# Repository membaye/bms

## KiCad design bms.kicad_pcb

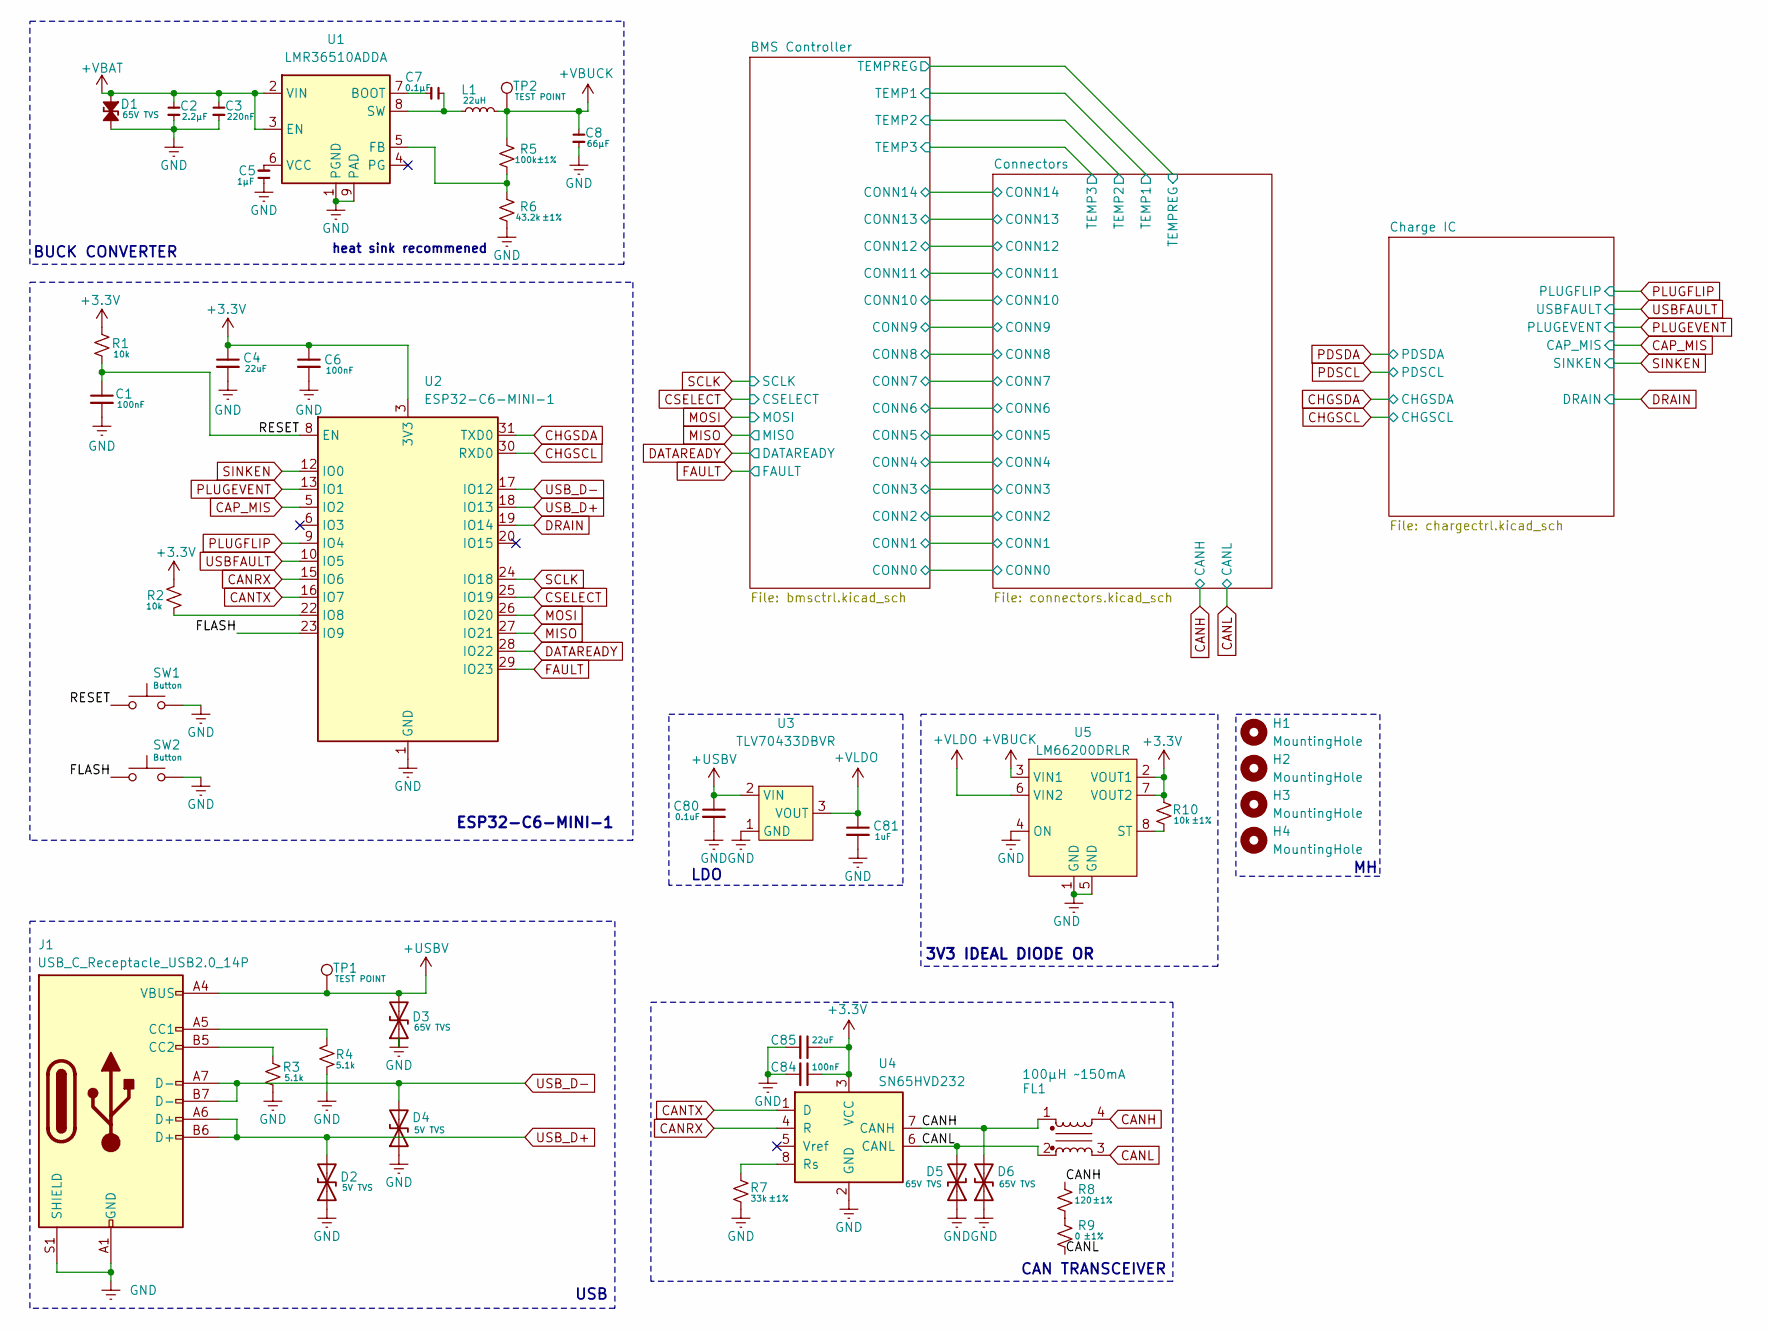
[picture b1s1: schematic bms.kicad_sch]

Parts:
C1, C6: 100nF; C_0402_1005Metric_Pad0.74x0.62mm_HandSolder; LCSC# C1525
C2: 2.2µF; C_0402_1005Metric_Pad0.74x0.62mm_HandSolder
C3: 220nF; C_0402_1005Metric_Pad0.74x0.62mm_HandSolder
C4, C85: 22uF; C_0402_1005Metric_Pad0.74x0.62mm_HandSolder; LCSC# C87997
C5: 1µF; C_0402_1005Metric_Pad0.74x0.62mm_HandSolder
C7: 0.1µF; C_0402_1005Metric_Pad0.74x0.62mm_HandSolder
C8: 66µF; C_0402_1005Metric_Pad0.74x0.62mm_HandSolder
C80: 0.1uF; C_0402_1005Metric_Pad0.74x0.62mm_HandSolder; LCSC# C87997
C81: 1uF; C_0402_1005Metric_Pad0.74x0.62mm_HandSolder; LCSC# C87997
C84: 100nF; C_0402_1005Metric_Pad0.74x0.62mm_HandSolder; LCSC# C87997
D1: 65V TVS; D_0402_1005Metric_Pad0.77x0.64mm_HandSolder
D2, D4: 5V TVS; D_0402_1005Metric_Pad0.77x0.64mm_HandSolder; LCSC# C316043
D3, D5, D6: 65V TVS; D_0402_1005Metric_Pad0.77x0.64mm_HandSolder; LCSC# C316043
FL1: 100µH ~150mA; Crystal_SMD_TXC_7M-4Pin_3.2x2.5mm; MPN C42394181
H1, H2, H3, H4: MountingHole; MountingHole_3.2mm_M3
J1: USB_C_Receptacle_USB2.0_14P; USB_C_Receptacle_GCT_USB4105-xx-A_16P_TopMnt_Horizontal; MPN C165948; LCSC# C165948
L1: 22uH; L_Ferrocore_DLG-0403; MPN C2929420
R1, R2: 10k; R_0402_1005Metric_Pad0.72x0.64mm_HandSolder; LCSC# C190095
R3, R4: 5.1k; R_0402_1005Metric_Pad0.72x0.64mm_HandSolder; LCSC# C490833
R5: 100k; R_0402_1005Metric_Pad0.72x0.64mm_HandSolder; Tolerance ±1%
R6: 43.2k; R_0402_1005Metric_Pad0.72x0.64mm_HandSolder; Tolerance ±1%
R7: 33k; R_0402_1005Metric_Pad0.72x0.64mm_HandSolder; Tolerance ±1%
R8: 120; R_0402_1005Metric_Pad0.72x0.64mm_HandSolder; Tolerance ±1%
R9: 0; R_0402_1005Metric_Pad0.72x0.64mm_HandSolder; Tolerance ±1%
R10: 10k; R_0402_1005Metric_Pad0.72x0.64mm_HandSolder; Tolerance ±1%
SW1, SW2: Button; SW-SMD_L3.9-W3.0-P4.45; LCSC# C720477
TP1, TP2: TEST POINT; TestPoint_Pad_1.0x1.0mm
U1: LMR36510ADDA; Texas_HTSOP-8-1EP_3.9x4.9mm_P1.27mm_EP2.95x4.9mm_Mask2.4x3.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
U2: ESP32-C6-MINI-1; LCSC# C5736265
U3: TLV70433DBVR; SOT-23-5_HandSoldering
U4: SN65HVD232; SOIC-8_3.9x4.9mm_P1.27mm
U5: LM66200DRLR; SOT-23-8

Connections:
+3.3V: C4.1, C6.1, C84.1, C85.1, R1.1, R2.1, R10.2, U2.3 (3V3), U4.3 (VCC), U5.2 (VOUT1), U5.7 (VOUT2); also elsewhere on the board
+USBV: C80.1, D3.2 (A2), J1.A4 (VBUS), J1.A9 (VBUS), J1.B4 (VBUS), J1.B9 (VBUS), TP1.1, U3.2 (VIN); also elsewhere on the board
+VBAT: C2.1, C3.1, D1.1 (A1), U1.2 (VIN), U1.3 (EN); also elsewhere on the board
+VBUCK: C8.1, L1.2, R5.1, TP2.1, U5.3 (VIN1)
+VLDO: C81.1, U3.3 (VOUT), U5.6 (VIN2)
/FLASH: SW2.1, U2.23 (IO9)
/RESET: C1.1, R1.2, SW1.1, U2.8 (EN)
CANH: D6.2 (A2), FL1.1, FL1.4, R8.2, U4.7 (CANH); also elsewhere on the board
CANL: D5.2 (A2), FL1.2, FL1.3, R9.1, U4.6 (CANL); also elsewhere on the board
CANRX: U2.15 (IO6), U4.4 (R)
CANTX: U2.16 (IO7), U4.1 (D)
CAP_MIS: U2.5 (IO2); also elsewhere on the board
CHGSCL: U2.30 (RXD0); also elsewhere on the board
CHGSDA: U2.31 (TXD0); also elsewhere on the board
CSELECT: U2.25 (IO19); also elsewhere on the board
DATAREADY: U2.28 (IO22); also elsewhere on the board
DRAIN: U2.19 (IO14); also elsewhere on the board
FAULT: U2.29 (IO23); also elsewhere on the board
GND: C1.2, C2.2, C3.2, C4.2, C5.1, C6.2, C8.2, C80.2, C81.2, C84.2, C85.2, D1.2 (A2), D2.1 (A1), D3.1 (A1), D4.1 (A1), D5.1 (A1), D6.1 (A1), J1.A1 (GND), J1.A12 (GND), J1.B1 (GND), J1.B12 (GND), J1.S1 (SHIELD), R3.2, R4.2, R6.2, R7.1, SW1.2, SW2.2, U1.1 (PGND), U1.9 (PAD), U2.1 (GND), U2.2 (GND), U2.11 (GND), U2.14 (GND), U2.36 (GND), U2.37 (GND), U2.38 (GND), U2.39 (GND), U2.40 (GND), U2.41 (GND), U2.42 (GND), U2.43 (GND), U2.44 (GND), U2.45 (GND), U2.46 (GND), U2.47 (GND), U2.48 (GND), U2.49 (GND), U2.50 (GND), U2.51 (GND), U2.52 (GND), U2.53 (GND), U3.1 (GND), U4.2 (GND), U5.1 (GND), U5.4 (ON), U5.5 (GND); also elsewhere on the board
MISO: U2.27 (IO21); also elsewhere on the board
MOSI: U2.26 (IO20); also elsewhere on the board
unnamed: J1.A5 (CC1), R4.1
unnamed: J1.B5 (CC2), R3.1
unnamed: R8.1, R9.2
unnamed: C7.2, U1.7 (BOOT)
unnamed: R5.2, R6.1, U1.5 (FB)
unnamed: C7.1, L1.1, U1.8 (SW)
unnamed: C5.2, U1.6 (VCC)
unnamed: R2.2, U2.22 (IO8)
unnamed: R7.2, U4.8 (Rs)
unnamed: R10.1, U5.8 (ST)
PLUGEVENT: U2.13 (IO1); also elsewhere on the board
PLUGFLIP: U2.9 (IO4); also elsewhere on the board
SCLK: U2.24 (IO18); also elsewhere on the board
SINKEN: U2.12 (IO0); also elsewhere on the board
USBFAULT: U2.10 (IO5); also elsewhere on the board
USB_D+: D2.2 (A2), J1.A6 (D+), J1.B6 (D+), U2.18 (IO13)
USB_D-: D4.2 (A2), J1.A7 (D-), J1.B7 (D-), U2.17 (IO12)

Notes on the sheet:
ESP32-C6-MINI-1
heat sink recommened
BUCK CONVERTER
USB
LDO
CAN TRANSCEIVER
3V3 IDEAL DIODE OR

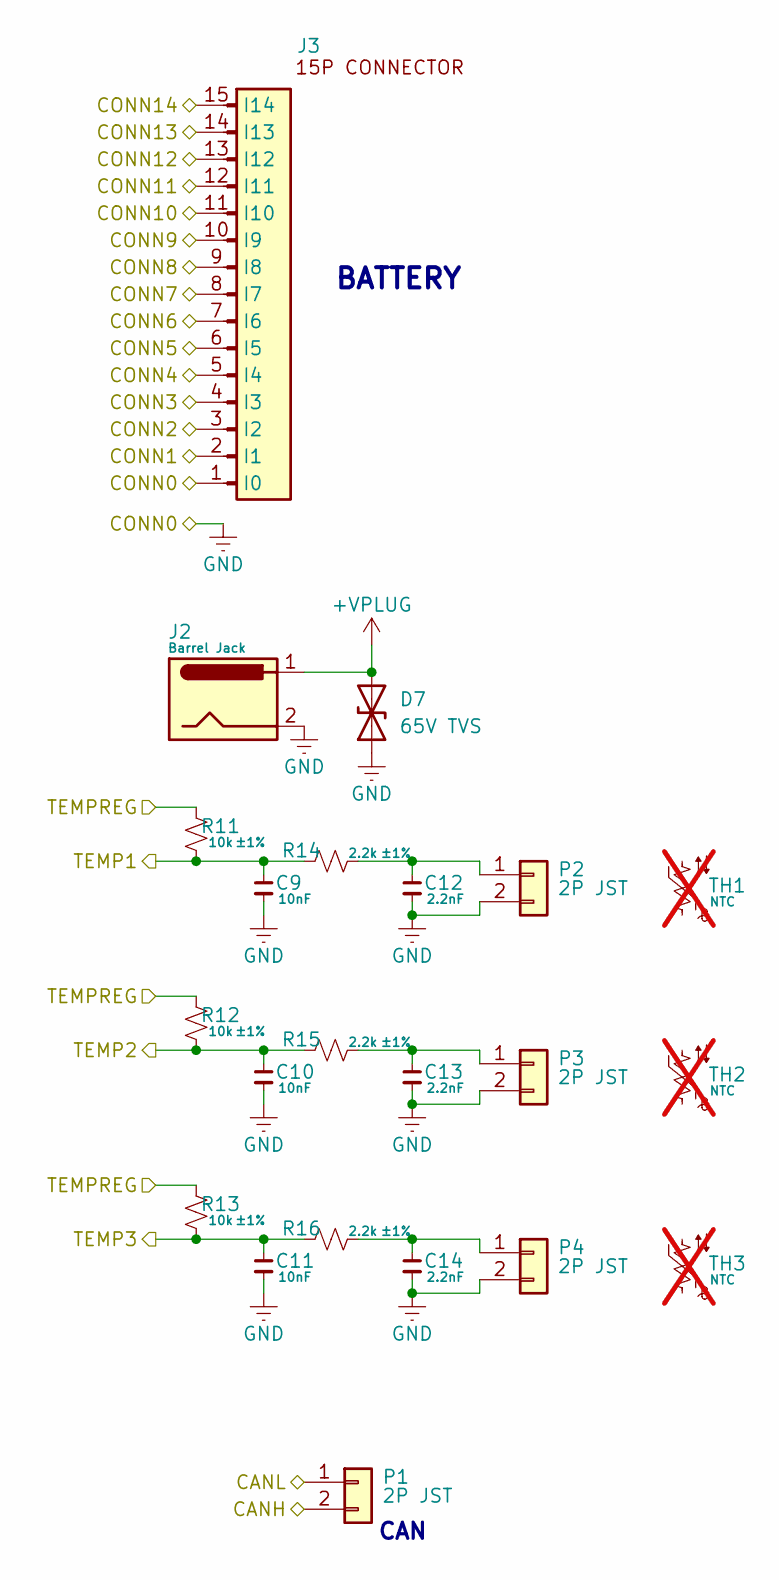
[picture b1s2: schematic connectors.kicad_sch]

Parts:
C9, C10, C11: 10nF; C_0402_1005Metric_Pad0.74x0.62mm_HandSolder
C12, C13, C14: 2.2nF; C_0402_1005Metric_Pad0.74x0.62mm_HandSolder
D7: 65V TVS; D_0402_1005Metric_Pad0.77x0.64mm_HandSolder; LCSC# C1973257
J2: Barrel Jack; BarrelJack_CUI_PJ-063AH_Horizontal
J3: 15P JST; CONN-SMD_15P-P1.25_SM15B-GHS-TB-LF-SN; MPN C265027
P1, P2, P3, P4: 2P JST; CONN-SMD_2P-P2.00_XUNPU_WAFER-PH2.0-2PWB; MPN C3029440; LCSC# C3029440
R11, R12, R13: 10k; R_0402_1005Metric_Pad0.72x0.64mm_HandSolder; Tolerance ±1%
R14, R15, R16: 2.2k; R_0402_1005Metric_Pad0.72x0.64mm_HandSolder; Tolerance ±1%
TH1, TH2, TH3: NTC; not fitted

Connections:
+VBAT: J3.15 (I14); also elsewhere on the board
+VPLUG: D7.2 (A2), J2.1; also elsewhere on the board
/BMS Controller/CONN1: J3.2 (I1); also elsewhere on the board
/BMS Controller/CONN2: J3.3 (I2); also elsewhere on the board
/BMS Controller/CONN3: J3.4 (I3); also elsewhere on the board
/BMS Controller/CONN4: J3.5 (I4); also elsewhere on the board
/BMS Controller/CONN5: J3.6 (I5); also elsewhere on the board
/BMS Controller/CONN6: J3.7 (I6); also elsewhere on the board
/BMS Controller/CONN7: J3.8 (I7); also elsewhere on the board
/BMS Controller/CONN8: J3.9 (I8); also elsewhere on the board
/BMS Controller/CONN9: J3.10 (I9); also elsewhere on the board
/BMS Controller/CONN10: J3.11 (I10); also elsewhere on the board
/BMS Controller/CONN11: J3.12 (I11); also elsewhere on the board
/BMS Controller/CONN12: J3.13 (I12); also elsewhere on the board
/BMS Controller/CONN13: J3.14 (I13); also elsewhere on the board
/BMS Controller/TEMP1: C9.1, R11.2, R14.1; also elsewhere on the board
/BMS Controller/TEMP2: C10.1, R12.2, R15.1; also elsewhere on the board
/BMS Controller/TEMP3: C11.1, R13.2, R16.1; also elsewhere on the board
/BMS Controller/TEMPREG: R11.1, R12.1, R13.1; also elsewhere on the board
CANH: P1.2; also elsewhere on the board
CANL: P1.1; also elsewhere on the board
GND: C9.2, C10.2, C11.2, C12.2, C13.2, C14.2, D7.1 (A1), J2.2, J3.1 (I0), P2.2, P3.2, P4.2; also elsewhere on the board
unnamed: C12.1, P2.1, R14.2
unnamed: C13.1, P3.1, R15.2
unnamed: C14.1, P4.1, R16.2

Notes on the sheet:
CAN
BATTERY

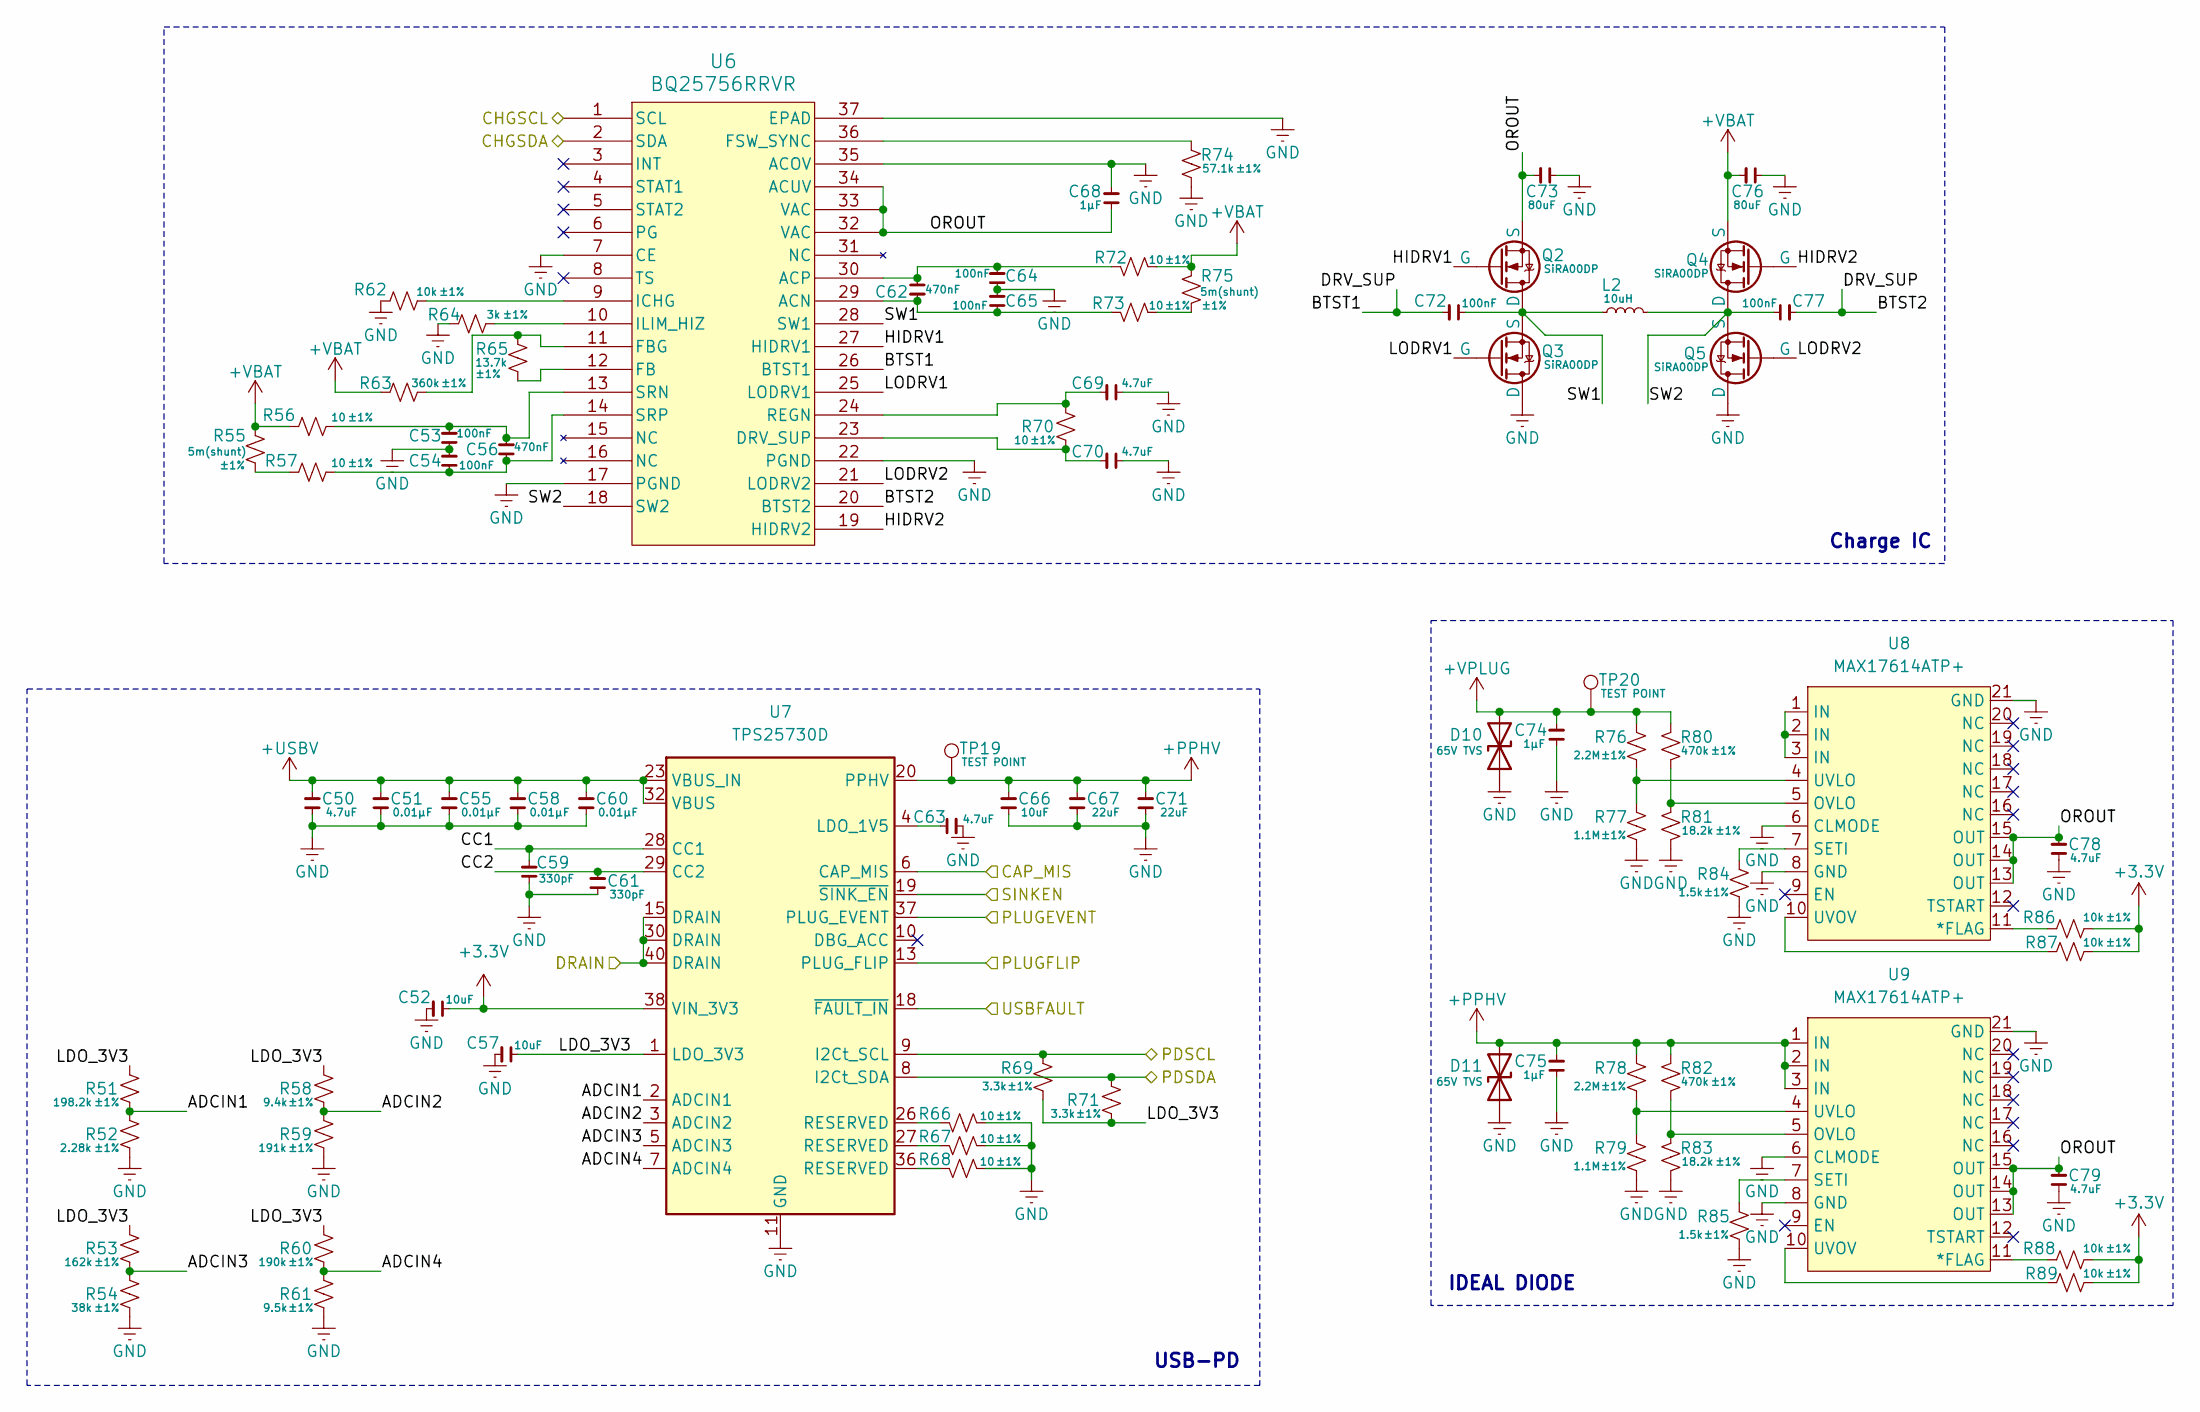
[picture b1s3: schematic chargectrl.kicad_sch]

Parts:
C50, C63, C69, C70, C78, C79: 4.7uF; C_0402_1005Metric_Pad0.74x0.62mm_HandSolder
C51, C55, C58, C60: 0.01µF; C_0402_1005Metric_Pad0.74x0.62mm_HandSolder
C52, C57, C66: 10uF; C_0402_1005Metric_Pad0.74x0.62mm_HandSolder
C53, C54, C64, C65, C72, C77: 100nF; C_0402_1005Metric_Pad0.74x0.62mm_HandSolder
C56, C62: 470nF; C_0402_1005Metric_Pad0.74x0.62mm_HandSolder
C59, C61: 330pF; C_0402_1005Metric_Pad0.74x0.62mm_HandSolder
C67, C71: 22uF; C_0402_1005Metric_Pad0.74x0.62mm_HandSolder
C68, C74, C75: 1µF; C_0402_1005Metric_Pad0.74x0.62mm_HandSolder
C73, C76: 80uF; C_0402_1005Metric_Pad0.74x0.62mm_HandSolder
D10, D11: 65V TVS; D_0402_1005Metric_Pad0.77x0.64mm_HandSolder; LCSC# C1973257
L2: 10uH; L_Sunlord_MWSA1205S-100; MPN C2847573
Q2, Q3, Q4, Q5: SiRA00DP; PowerPAK_SO-8_Single; MPN C141540
R51: 198.2k; R_0402_1005Metric_Pad0.72x0.64mm_HandSolder; Tolerance ±1%
R52: 2.28k; R_0402_1005Metric_Pad0.72x0.64mm_HandSolder; Tolerance ±1%
R53: 162k; R_0402_1005Metric_Pad0.72x0.64mm_HandSolder; Tolerance ±1%
R54: 38k; R_0402_1005Metric_Pad0.72x0.64mm_HandSolder; Tolerance ±1%
R55, R75: 5m(shunt); R_0402_1005Metric_Pad0.72x0.64mm_HandSolder; Tolerance ±1%
R56, R57, R66, R67, R68, R70, R72, R73: 10; R_0402_1005Metric_Pad0.72x0.64mm_HandSolder; Tolerance ±1%
R58: 9.4k; R_0402_1005Metric_Pad0.72x0.64mm_HandSolder; Tolerance ±1%
R59: 191k; R_0402_1005Metric_Pad0.72x0.64mm_HandSolder; Tolerance ±1%
R60: 190k; R_0402_1005Metric_Pad0.72x0.64mm_HandSolder; Tolerance ±1%
R61: 9.5k; R_0402_1005Metric_Pad0.72x0.64mm_HandSolder; Tolerance ±1%
R62, R86, R87, R88, R89: 10k; R_0402_1005Metric_Pad0.72x0.64mm_HandSolder; Tolerance ±1%
R63: 360k; R_0402_1005Metric_Pad0.72x0.64mm_HandSolder; Tolerance ±1%
R64: 3k; R_0402_1005Metric_Pad0.72x0.64mm_HandSolder; Tolerance ±1%
R65: 13.7k; R_0402_1005Metric_Pad0.72x0.64mm_HandSolder; Tolerance ±1%
R69, R71: 3.3k; R_0402_1005Metric_Pad0.72x0.64mm_HandSolder; Tolerance ±1%
R74: 57.1k; R_0402_1005Metric_Pad0.72x0.64mm_HandSolder; Tolerance ±1%
R76, R78: 2.2M; R_0402_1005Metric_Pad0.72x0.64mm_HandSolder; Tolerance ±1%
R77, R79: 1.1M; R_0402_1005Metric_Pad0.72x0.64mm_HandSolder; Tolerance ±1%
R80, R82: 470k; R_0402_1005Metric_Pad0.72x0.64mm_HandSolder; Tolerance ±1%
R81, R83: 18.2k; R_0402_1005Metric_Pad0.72x0.64mm_HandSolder; Tolerance ±1%
R84, R85: 1.5k; R_0402_1005Metric_Pad0.72x0.64mm_HandSolder; Tolerance ±1%
TP19, TP20: TEST POINT; TestPoint_Pad_1.0x1.0mm
U6: BQ25756RRVR; MPN C19272232
U7: TPS25730D; Texas_REF0038A_WQFN-38-2EP_6x4mm_P0.4; MPN C22438973
U8, U9: MAX17614ATP+; TQFN-20-1EP_4x4mm_P0.5mm_EP2.7x2.7mm; MPN C18185409

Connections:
+3.3V: C52.1, R86.2, R87.2, R88.2, R89.2, U7.38 (VIN_3V3); also elsewhere on the board
+PPHV: C66.2, C67.2, C71.2, C75.2, D11.2 (A2), R78.1, R82.1, TP19.1, U7.20 (PPHV), U9.1 (IN), U9.2 (IN), U9.3 (IN)
+USBV: C50.2, C51.2, C55.2, C58.2, C60.2, U7.23 (VBUS_IN), U7.32 (VBUS); also elsewhere on the board
+VBAT: C76.2, Q4.3 (S), R55.1, R56.1, R63.2, R72.1, R75.1; also elsewhere on the board
+VPLUG: C74.2, D10.2 (A2), R76.1, R80.1, TP20.1; also elsewhere on the board
/Charge IC/ADCIN1: R51.2, R52.1, U7.2 (ADCIN1)
/Charge IC/ADCIN2: R58.2, R59.1, U7.3 (ADCIN2)
/Charge IC/ADCIN3: R53.2, R54.1, U7.5 (ADCIN3)
/Charge IC/ADCIN4: R60.2, R61.1, U7.7 (ADCIN4)
/Charge IC/BTST1: C72.2, C77.2, U6.20 (BTST2), U6.26 (BTST1)
/Charge IC/CC1: C59.2, U7.28 (CC1)
/Charge IC/CC2: C61.2, U7.29 (CC2)
/Charge IC/HIDRV1: Q2.2 (G), U6.27 (HIDRV1)
/Charge IC/HIDRV2: Q4.2 (G), U6.19 (HIDRV2)
/Charge IC/LDO_3V3: C57.1, R51.1, R53.1, R58.1, R60.1, R69.2, R71.2, U7.1 (LDO_3V3)
/Charge IC/LODRV1: Q3.2 (G), U6.25 (LODRV1)
/Charge IC/LODRV2: Q5.2 (G), U6.21 (LODRV2)
/Charge IC/OROUT: C68.1, C73.2, C78.2, C79.2, Q2.3 (S), U6.32 (VAC), U6.33 (VAC), U6.34 (ACUV), U8.13 (OUT), U8.14 (OUT), U8.15 (OUT), U9.13 (OUT), U9.14 (OUT), U9.15 (OUT)
/Charge IC/SW1: C72.1, L2.1, Q2.1 (D), Q3.3 (S), U6.28 (SW1)
/Charge IC/SW2: C77.1, L2.2, Q4.1 (D), Q5.3 (S), U6.18 (SW2)
CAP_MIS: U7.6 (CAP_MIS); also elsewhere on the board
CHGSCL: U6.1 (SCL); also elsewhere on the board
CHGSDA: U6.2 (SDA); also elsewhere on the board
DRAIN: U7.15 (DRAIN), U7.30 (DRAIN), U7.40 (DRAIN); also elsewhere on the board
GND: C50.1, C51.1, C52.2, C53.1, C54.2, C55.1, C57.2, C58.1, C59.1, C60.1, C61.1, C63.2, C64.1, C65.2, C66.1, C67.1, C68.2, C69.1, C70.1, C71.1, C73.1, C74.1, C75.1, C76.1, C78.1, C79.1, D10.1 (A1), D11.1 (A1), Q3.1 (D), Q5.1 (D), R52.2, R54.2, R59.2, R61.2, R62.1, R64.2, R66.1, R67.1, R68.1, R74.1, R77.2, R79.2, R81.2, R83.2, R84.2, R85.2, U6.7 (CE), U6.17 (PGND), U6.22 (PGND), U6.35 (ACOV), U6.37 (EPAD), U7.11 (GND), U7.12 (GND), U7.14 (GND), U7.16 (GND), U7.17 (GND), U7.31 (GND), U7.34 (GND), U7.39 (GND), U8.6 (CLMODE), U8.8 (GND), U8.21 (GND), U9.6 (CLMODE), U9.8 (GND), U9.21 (GND); also elsewhere on the board
unnamed: R55.2, R57.1
unnamed: R66.2, U7.26 (RESERVED)
unnamed: R67.2, U7.27 (RESERVED)
unnamed: R68.2, U7.36 (RESERVED)
unnamed: R73.1, R75.2
unnamed: C62.2, C65.1, R73.2, U6.29 (ACN)
unnamed: C62.1, C64.2, R72.2, U6.30 (ACP)
unnamed: C70.2, R70.2, U6.23 (DRV_SUP)
unnamed: R65.2, U6.12 (FB)
unnamed: R63.1, R65.1, U6.11 (FBG)
unnamed: R74.2, U6.36 (FSW_SYNC)
unnamed: R62.2, U6.9 (ICHG)
unnamed: R64.1, U6.10 (ILIM_HIZ)
unnamed: C69.2, R70.1, U6.24 (REGN)
unnamed: C53.2, C56.2, R56.2, U6.13 (SRN)
unnamed: C54.1, C56.1, R57.2, U6.14 (SRP)
unnamed: C63.1, U7.4 (LDO_1V5)
unnamed: R86.1, U8.11 (*FLAG)
unnamed: U8.1 (IN), U8.2 (IN), U8.3 (IN)
unnamed: R80.2, R81.1, U8.5 (OVLO)
unnamed: R84.1, U8.7 (SETI)
unnamed: R76.2, R77.1, U8.4 (UVLO)
unnamed: R87.1, U8.10 (UVOV)
unnamed: R88.1, U9.11 (*FLAG)
unnamed: R82.2, R83.1, U9.5 (OVLO)
unnamed: R85.1, U9.7 (SETI)
unnamed: R78.2, R79.1, U9.4 (UVLO)
unnamed: R89.1, U9.10 (UVOV)
PDSCL: R69.1, U7.9 (I2Ct_SCL)
PDSDA: R71.1, U7.8 (I2Ct_SDA)
PLUGEVENT: U7.37 (PLUG_EVENT); also elsewhere on the board
PLUGFLIP: U7.13 (PLUG_FLIP); also elsewhere on the board
SINKEN: U7.19 (~SINK_EN); also elsewhere on the board
USBFAULT: U7.18 (~FAULT_IN); also elsewhere on the board

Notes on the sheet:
IDEAL DIODE
USB-PD
Charge IC

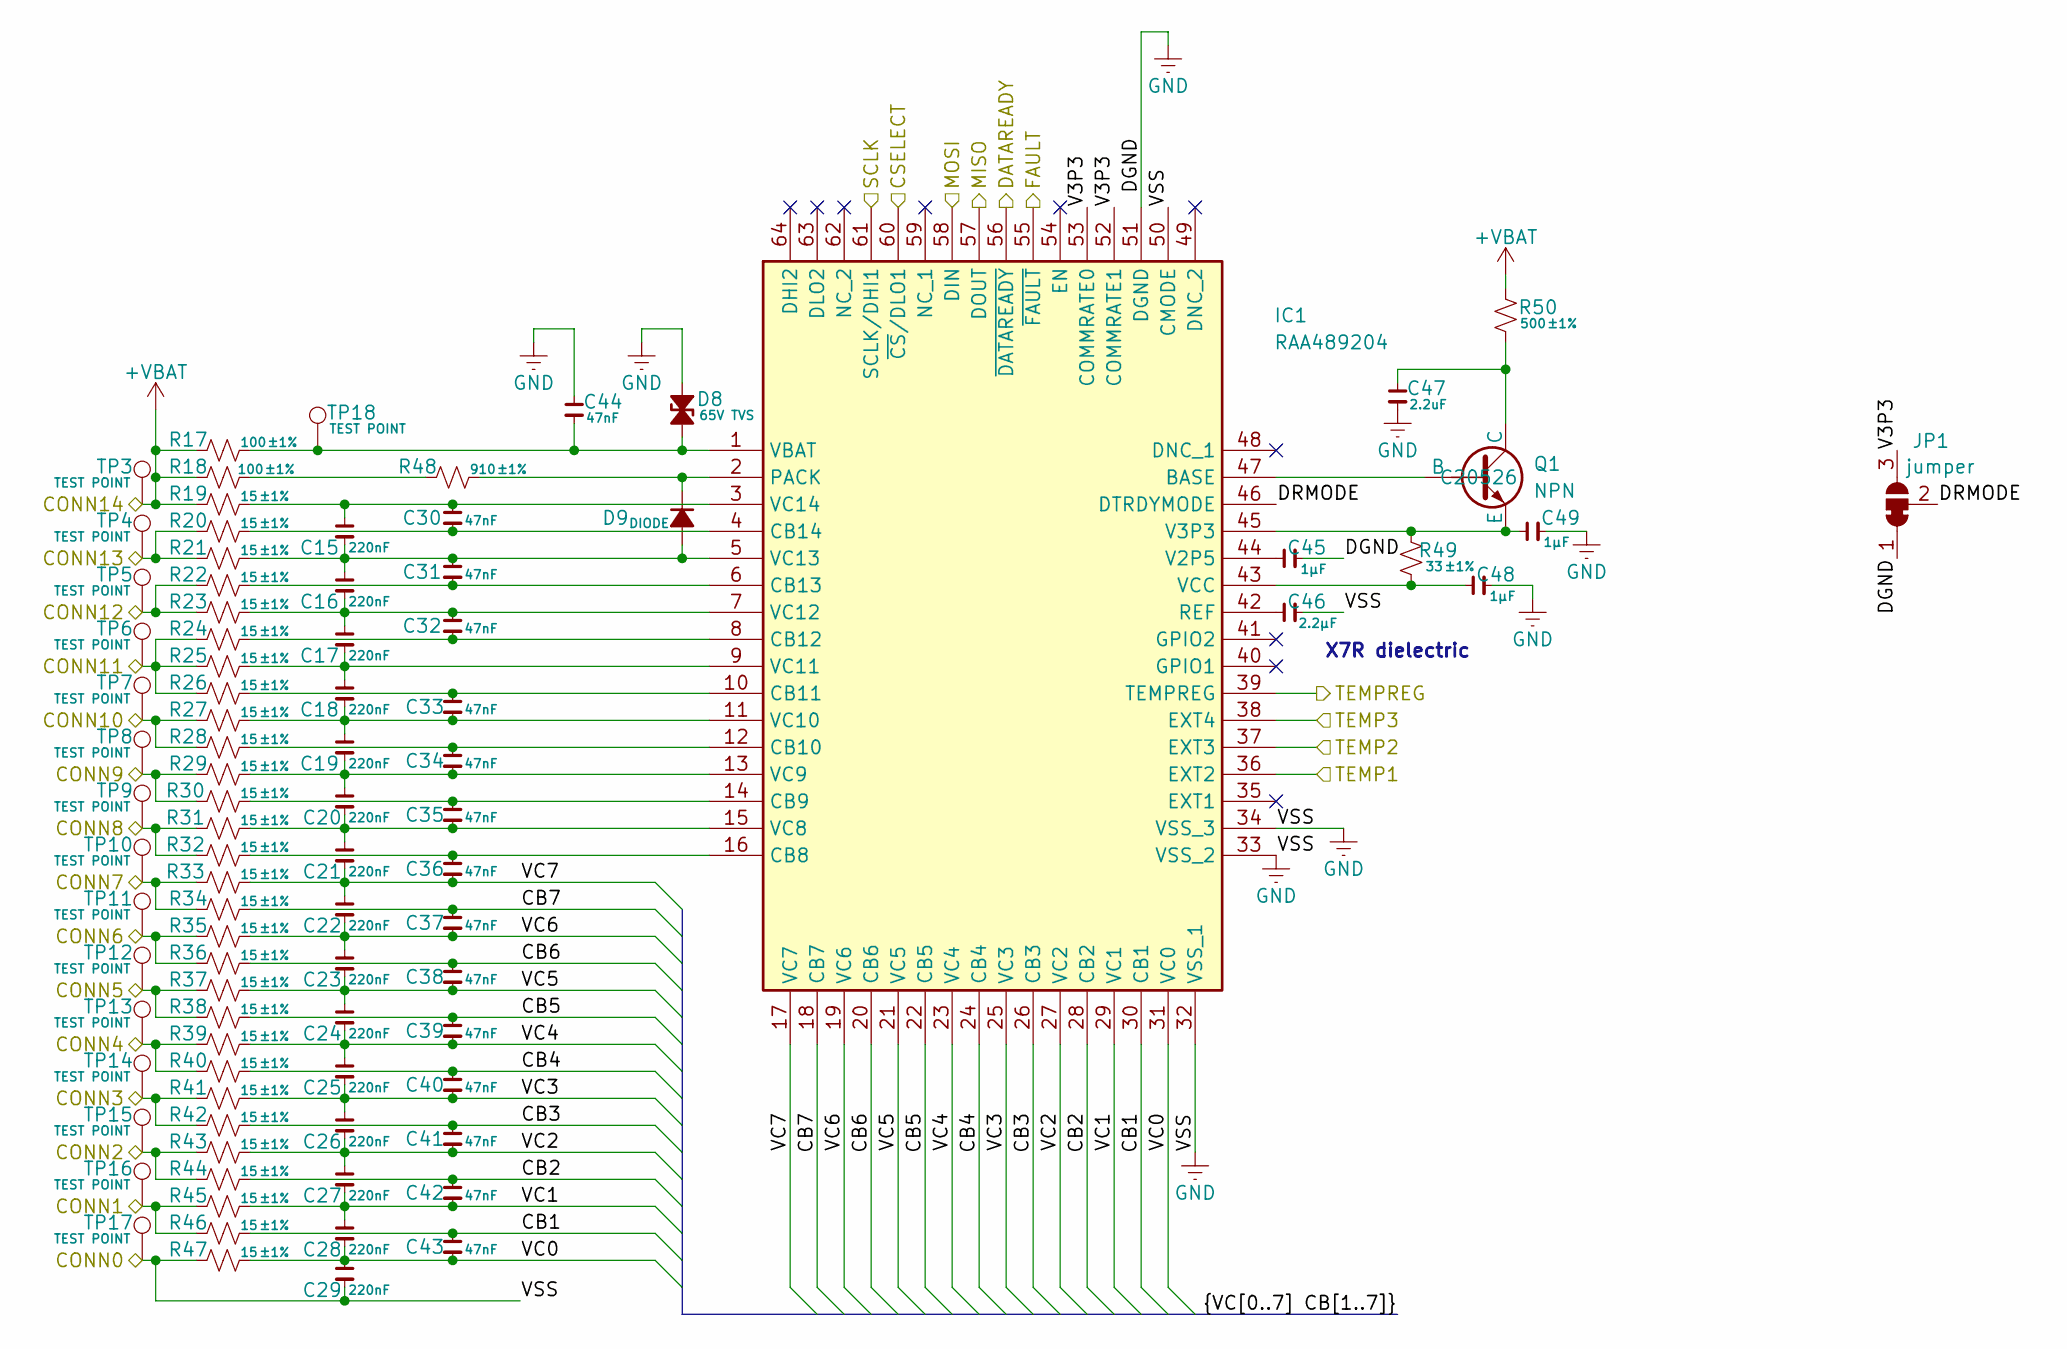
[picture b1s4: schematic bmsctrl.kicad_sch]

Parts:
C15, C16, C17, C18, C19, C20, C21, C22, C23, C24, C25, C26, C27, C28, C29: 220nF; C_0402_1005Metric_Pad0.74x0.62mm_HandSolder
C30, C31, C32, C33, C34, C35, C36, C37, C38, C39, C40, C41, C42, C43, C44: 47nF; C_0402_1005Metric_Pad0.74x0.62mm_HandSolder
C45, C48, C49: 1µF; C_0402_1005Metric_Pad0.74x0.62mm_HandSolder
C46: 2.2µF; C_0402_1005Metric_Pad0.74x0.62mm_HandSolder
C47: 2.2uF; C_0402_1005Metric_Pad0.74x0.62mm_HandSolder
D8: 65V TVS; D_0402_1005Metric_Pad0.77x0.64mm_HandSolder
D9: DIODE; D_0402_1005Metric_Pad0.77x0.64mm_HandSolder
IC1: RAA489204; QFP50P1200X1200X120-64N; Mouser Part Number 968-RAA4892042GFTAA0
JP1: jumper; SolderJumper-3_P1.3mm_Bridged12_RoundedPad1.0x1.5mm
Q1: NPN; SOT-23; MPN C20526
R17, R18: 100; R_0402_1005Metric_Pad0.72x0.64mm_HandSolder; Tolerance ±1%
R19, R20, R21, R22, R23, R24, R25, R26, R27, R28, R29, R30, R31, R32, R33, R34, R35, R36, R37, R38, R39, R40, R41, R42, R43, R44, R45, R46, R47: 15; R_0402_1005Metric_Pad0.72x0.64mm_HandSolder; Tolerance ±1%
R48: 910; R_0402_1005Metric_Pad0.72x0.64mm_HandSolder; Tolerance ±1%
R49: 33; R_0402_1005Metric_Pad0.72x0.64mm_HandSolder; Tolerance ±1%
R50: 500; R_0402_1005Metric_Pad0.72x0.64mm_HandSolder; Tolerance ±1%
TP3, TP4, TP5, TP6, TP7, TP8, TP9, TP10, TP11, TP12, TP13, TP14, TP15, TP16, TP17, TP18: TEST POINT; TestPoint_Pad_1.0x1.0mm

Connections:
+VBAT: R17.1, R18.1, R19.1, R50.2, TP3.1; also elsewhere on the board
/BMS Controller/CB1: C43.1, IC1.30 (CB1), R46.2
/BMS Controller/CB2: C42.1, IC1.28 (CB2), R44.2
/BMS Controller/CB3: C41.1, IC1.26 (CB3), R42.2
/BMS Controller/CB4: C40.1, IC1.24 (CB4), R40.2
/BMS Controller/CB5: C39.1, IC1.22 (CB5), R38.2
/BMS Controller/CB6: C38.1, IC1.20 (CB6), R36.2
/BMS Controller/CB7: C37.1, IC1.18 (CB7), R34.2
/BMS Controller/CONN1: R45.1, R46.1, TP16.1; also elsewhere on the board
/BMS Controller/CONN2: R43.1, R44.1, TP15.1; also elsewhere on the board
/BMS Controller/CONN3: R41.1, R42.1, TP14.1; also elsewhere on the board
/BMS Controller/CONN4: R39.1, R40.1, TP13.1; also elsewhere on the board
/BMS Controller/CONN5: R37.1, R38.1, TP12.1; also elsewhere on the board
/BMS Controller/CONN6: R35.1, R36.1, TP11.1; also elsewhere on the board
/BMS Controller/CONN7: R33.1, R34.1, TP10.1; also elsewhere on the board
/BMS Controller/CONN8: R31.1, R32.1, TP9.1; also elsewhere on the board
/BMS Controller/CONN9: R29.1, R30.1, TP8.1; also elsewhere on the board
/BMS Controller/CONN10: R27.1, R28.1, TP7.1; also elsewhere on the board
/BMS Controller/CONN11: R24.1, R25.1, R26.1, TP6.1; also elsewhere on the board
/BMS Controller/CONN12: R22.1, R23.1, TP5.1; also elsewhere on the board
/BMS Controller/CONN13: R20.1, R21.1, TP4.1; also elsewhere on the board
/BMS Controller/DRMODE: IC1.46 (DTRDYMODE), JP1.2 (C)
/BMS Controller/TEMP1: IC1.36 (EXT2); also elsewhere on the board
/BMS Controller/TEMP2: IC1.37 (EXT3); also elsewhere on the board
/BMS Controller/TEMP3: IC1.38 (EXT4); also elsewhere on the board
/BMS Controller/TEMPREG: IC1.39 (TEMPREG); also elsewhere on the board
/BMS Controller/V3P3: IC1.52 (COMMRATE1), IC1.53 (COMMRATE0), JP1.3 (B)
/BMS Controller/VC0: C28.2, C29.1, C43.2, IC1.31 (VC0), R47.2
/BMS Controller/VC1: C27.2, C28.1, C42.2, IC1.29 (VC1), R45.2
/BMS Controller/VC2: C26.2, C27.1, C41.2, IC1.27 (VC2), R43.2
/BMS Controller/VC3: C25.2, C26.1, C40.2, IC1.25 (VC3), R41.2
/BMS Controller/VC4: C24.2, C25.1, C39.2, IC1.23 (VC4), R39.2
/BMS Controller/VC5: C23.2, C24.1, C38.2, IC1.21 (VC5), R37.2
/BMS Controller/VC6: C22.2, C23.1, C37.2, IC1.19 (VC6), R35.2
/BMS Controller/VC7: C21.2, C22.1, C36.2, IC1.17 (VC7), R33.2
CSELECT: IC1.60 (~CS/DLO1); also elsewhere on the board
DATAREADY: IC1.56 (~DATAREADY); also elsewhere on the board
FAULT: IC1.55 (~FAULT); also elsewhere on the board
GND: C29.2, C44.1, C45.2, C46.2, C47.2, C48.2, C49.2, D8.1 (A1), IC1.32 (VSS_1), IC1.33 (VSS_2), IC1.34 (VSS_3), IC1.50 (CMODE), IC1.51 (DGND), JP1.1 (A), R47.1, TP17.1; also elsewhere on the board
MISO: IC1.57 (DOUT); also elsewhere on the board
MOSI: IC1.58 (DIN); also elsewhere on the board
unnamed: C44.2, D8.2 (A2), IC1.1 (VBAT), R17.2, TP18.1
unnamed: C15.2, C16.1, C31.1, D9.2 (A), IC1.5 (VC13), R21.2
unnamed: D9.1 (K), IC1.2 (PACK), R48.2
unnamed: IC1.47 (BASE), Q1.2 (B)
unnamed: C36.1, IC1.16 (CB8), R32.2
unnamed: C35.1, IC1.14 (CB9), R30.2
unnamed: C34.1, IC1.12 (CB10), R28.2
unnamed: C33.1, IC1.10 (CB11), R26.2
unnamed: C32.2, IC1.8 (CB12), R24.2
unnamed: C31.2, IC1.6 (CB13), R22.2
unnamed: C30.2, IC1.4 (CB14), R20.2
unnamed: C46.1, IC1.42 (REF)
unnamed: C45.1, IC1.44 (V2P5)
unnamed: C49.1, IC1.45 (V3P3), Q1.3 (E), R49.2
unnamed: C20.2, C21.1, C35.2, IC1.15 (VC8), R31.2
unnamed: C19.2, C20.1, C34.2, IC1.13 (VC9), R29.2
unnamed: C18.2, C19.1, C33.2, IC1.11 (VC10), R27.2
unnamed: C17.2, C18.1, IC1.9 (VC11), R25.2
unnamed: C16.2, C17.1, C32.1, IC1.7 (VC12), R23.2
unnamed: C15.1, C30.1, IC1.3 (VC14), R19.2
unnamed: C48.1, IC1.43 (VCC), R49.1
unnamed: C47.1, Q1.1 (C), R50.1
unnamed: R18.2, R48.1
SCLK: IC1.61 (SCLK/DHI1); also elsewhere on the board

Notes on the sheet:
X7R dielectric

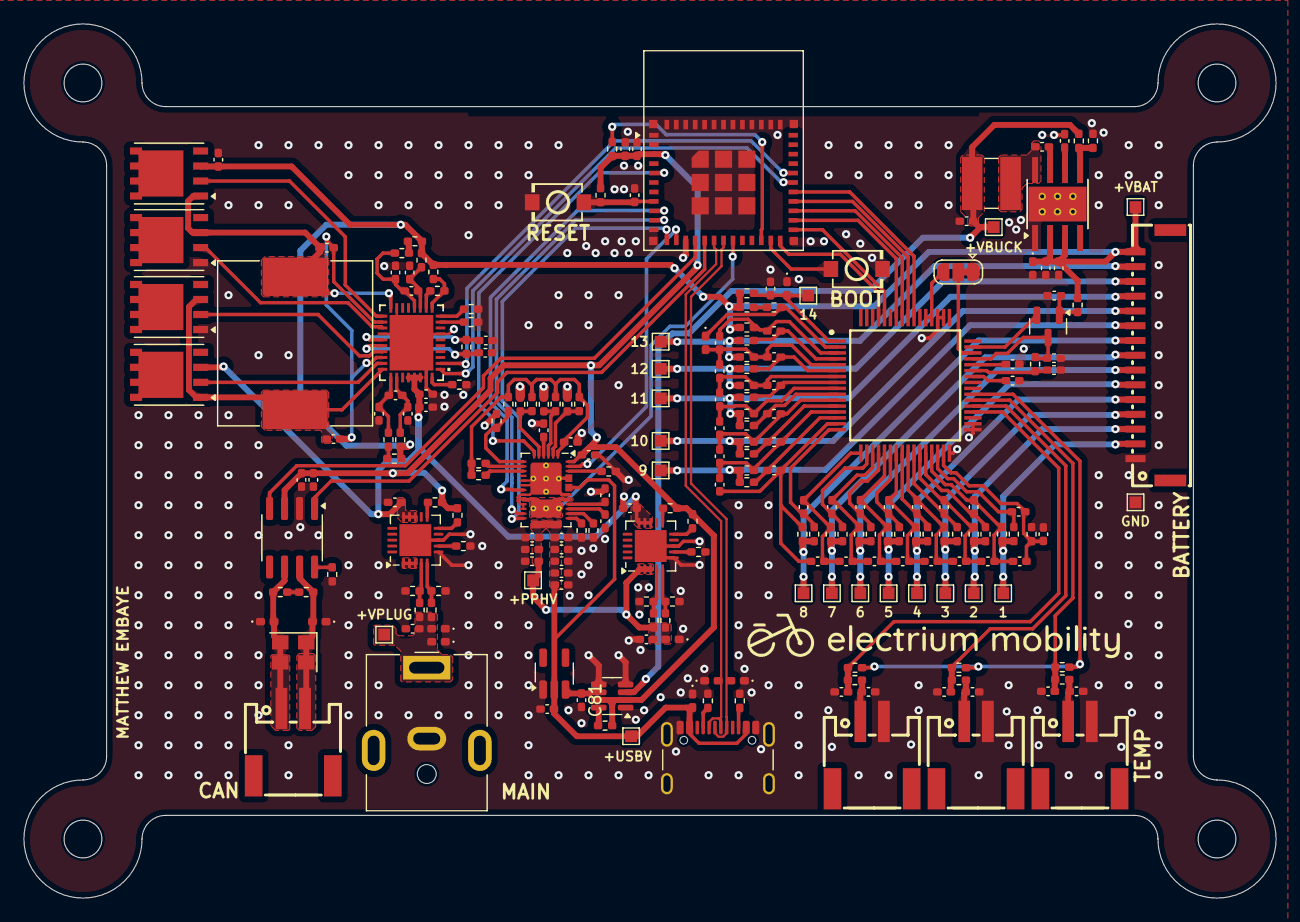
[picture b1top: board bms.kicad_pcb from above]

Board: 4 copper layers, 106.0 x 74.0 mm, 235 parts (0 on the bottom side), 145 nets.

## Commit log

2025-04-16 Finalized V2
2025-04-18 Finalized design for review and order
2025-04-22 Fixed Ideal Diodes
2025-04-23 EM-BMS1
    good to order!
